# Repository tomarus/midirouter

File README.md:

FPGA/Verilog MIDI Mixer
=======================

See also: 

* https://github.com/tomarus/v-midi
* https://github.com/tomarus/midiseq

This is a "production" version of my FPGA MIDI router.

My v-midi project is more experimental, this one is tuned for my own hardware.

# Disclaimer

Do not use this to learn Verilog or FPGA stuff.

This is my own personal experimental project.

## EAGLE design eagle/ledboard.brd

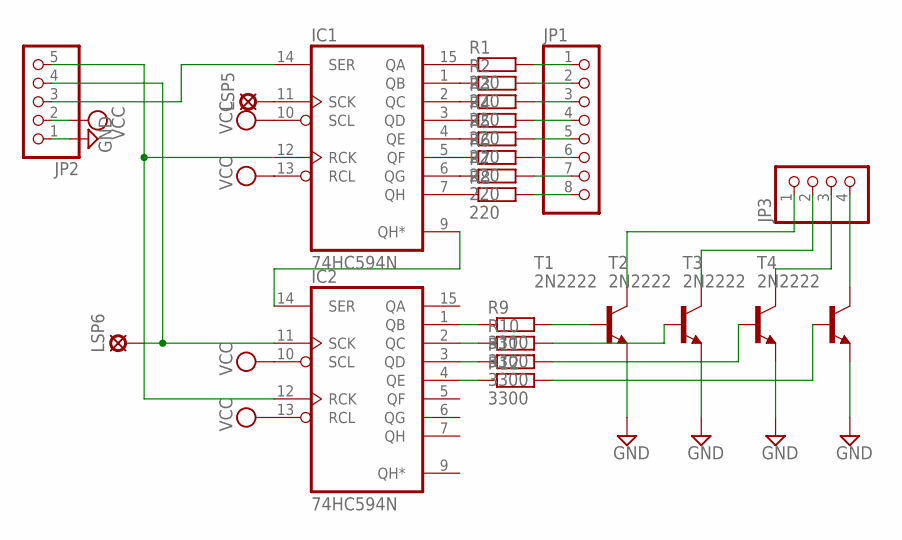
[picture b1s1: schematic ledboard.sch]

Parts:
IC1, IC2: 74HC594N; DIL16
JP1: PINHD-1X8; 1X08
JP2: PINHD-1X5; 1X05
JP3: PINHD-1X4; 1X04
LSP5, LSP6: LSP10
R1, R2, R3, R4, R5, R6, R7, R8: 220; 0207/10
R9, R10, R11, R12: 3300; 0207/10
T1, T2, T3, T4: 2N2222; TO92-EBC-OVAL

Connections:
GND: IC1.8 (GND), IC2.8 (GND), JP2.1, T1.E, T2.E, T3.E, T4.E
unnamed: IC1.14 (SER), JP2.3
unnamed: IC1.11 (SCK), LSP5.MP
unnamed: IC1.15 (QA), R1.1
unnamed: IC1.1 (QB), R2.1
unnamed: IC1.2 (QC), R3.1
unnamed: IC1.3 (QD), R4.1
unnamed: IC1.4 (QE), R5.1
unnamed: IC1.5 (QF), R6.1
unnamed: IC1.6 (QG), R7.1
unnamed: IC1.7 (QH), R8.1
unnamed: IC2.3 (QD), R11.1
unnamed: IC2.2 (QC), R10.1
unnamed: IC2.1 (QB), R9.1
unnamed: IC2.4 (QE), R12.1
unnamed: R9.2, T1.B
unnamed: R10.2, T2.B
unnamed: R11.2, T3.B
unnamed: R12.2, T4.B
unnamed: JP1.1, R1.2
unnamed: JP1.2, R2.2
unnamed: JP1.3, R3.2
unnamed: JP1.4, R4.2
unnamed: JP1.5, R5.2
unnamed: JP1.6, R6.2
unnamed: JP1.7, R7.2
unnamed: JP1.8, R8.2
unnamed: JP3.1, T1.C
unnamed: JP3.2, T2.C
unnamed: JP3.3, T3.C
unnamed: JP3.4, T4.C
unnamed: IC2.11 (SCK), JP2.4, LSP6.MP
unnamed: IC1.12 (RCK), IC2.12 (RCK), JP2.5
unnamed: IC1.9 (QH*), IC2.14 (SER)
VCC: IC1.10 (SCL), IC1.13 (RCL), IC1.16 (VCC), IC2.10 (SCL), IC2.13 (RCL), IC2.16 (VCC), JP2.2

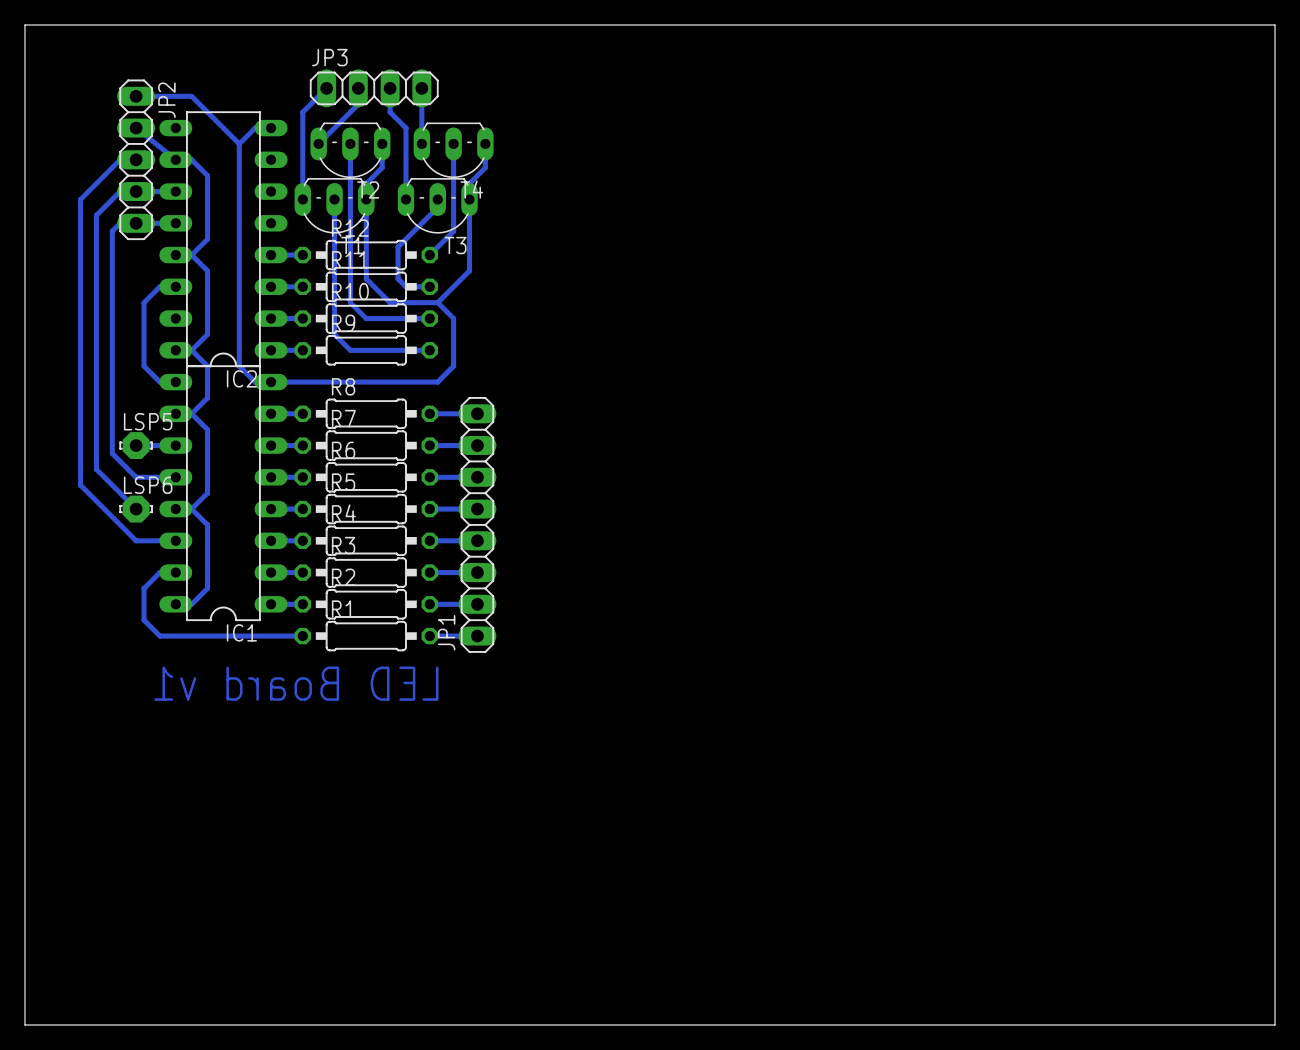
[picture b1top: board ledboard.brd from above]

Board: 2 copper layers, 100.0 x 80.0 mm, 23 parts (0 on the bottom side), 35 nets.

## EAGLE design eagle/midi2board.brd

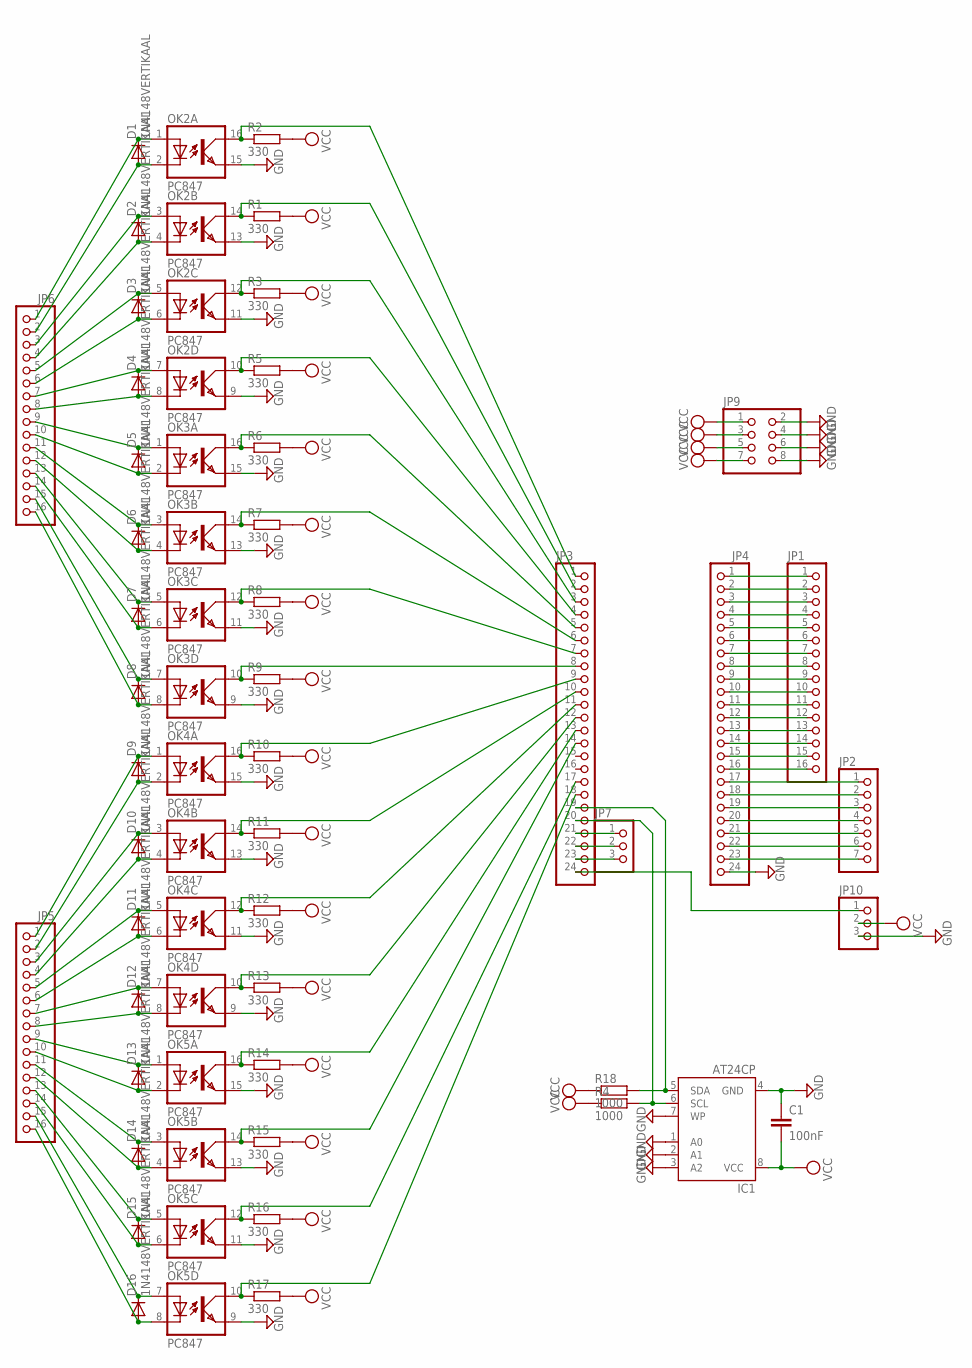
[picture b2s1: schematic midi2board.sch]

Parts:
C1: 100nF; C5B2.5
D1, D2, D3, D4, D5, D6, D7, D8, D9, D10, D11, D12, D13, D14, D15, D16: 1N4148VERTIKAAL; RAD2,5
IC1: AT24CP; DIL08
JP1, JP5, JP6: PINHD-1X16; 1X16
JP2: PINHD-1X7; 1X07
JP3, JP4: PINHD-1X24; 1X24
JP7, JP10: PINHD-1X3; 1X03
JP9: PINHD-2X4; 2X04
OK2, OK3, OK4, OK5: PC847; DIL16
R1, R2, R3, R5, R6, R7, R8, R9, R10, R11, R12, R13, R14, R15, R16, R17: 330; 0207/10
R4, R18: 1000; 0207/10

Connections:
GND: C1.1, IC1.1 (A0), IC1.2 (A1), IC1.3 (A2), IC1.4 (GND), IC1.7 (WP), JP4.24, JP9.2, JP9.4, JP9.6, JP9.8, JP10.3, OK2.9 (EMIT), OK2.11 (EMIT), OK2.13 (EMIT), OK2.15 (EMIT), OK3.9 (EMIT), OK3.11 (EMIT), OK3.13 (EMIT), OK3.15 (EMIT), OK4.9 (EMIT), OK4.11 (EMIT), OK4.13 (EMIT), OK4.15 (EMIT), OK5.9 (EMIT), OK5.11 (EMIT), OK5.13 (EMIT), OK5.15 (EMIT)
unnamed: JP2.1, JP4.17
unnamed: D1.C, JP6.1, OK2.1 (A)
unnamed: D1.A, JP6.2, OK2.2 (C)
unnamed: JP2.2, JP4.18
unnamed: JP2.3, JP4.19
unnamed: D2.C, JP6.3, OK2.3 (A)
unnamed: D2.A, JP6.4, OK2.4 (C)
unnamed: JP2.4, JP4.20
unnamed: D3.C, JP6.5, OK2.5 (A)
unnamed: D3.A, JP6.6, OK2.6 (C)
unnamed: D4.C, JP6.7, OK2.7 (A)
unnamed: D4.A, JP6.8, OK2.8 (C)
unnamed: D5.C, JP6.9, OK3.1 (A)
unnamed: D5.A, JP6.10, OK3.2 (C)
unnamed: D6.C, JP6.11, OK3.3 (A)
unnamed: D6.A, JP6.12, OK3.4 (C)
unnamed: D7.C, JP6.13, OK3.5 (A)
unnamed: D7.A, JP6.14, OK3.6 (C)
unnamed: D8.C, JP6.15, OK3.7 (A)
unnamed: D8.A, JP6.16, OK3.8 (C)
unnamed: D9.C, JP5.1, OK4.1 (A)
unnamed: D9.A, JP5.2, OK4.2 (C)
unnamed: D10.C, JP5.3, OK4.3 (A)
unnamed: D10.A, JP5.4, OK4.4 (C)
unnamed: D11.C, JP5.5, OK4.5 (A)
unnamed: D11.A, JP5.6, OK4.6 (C)
unnamed: D12.C, JP5.7, OK4.7 (A)
unnamed: D12.A, JP5.8, OK4.8 (C)
unnamed: D13.C, JP5.9, OK5.1 (A)
unnamed: D13.A, JP5.10, OK5.2 (C)
unnamed: D14.C, JP5.11, OK5.3 (A)
unnamed: D14.A, JP5.12, OK5.4 (C)
unnamed: D15.C, JP5.13, OK5.5 (A)
unnamed: D15.A, JP5.14, OK5.6 (C)
unnamed: D16.C, JP5.15, OK5.7 (A)
unnamed: D16.A, JP5.16, OK5.8 (C)
unnamed: JP3.2, OK2.14 (COL), R1.1
unnamed: JP3.1, OK2.16 (COL), R2.1
unnamed: JP3.3, OK2.12 (COL), R3.1
unnamed: JP3.4, OK2.10 (COL), R5.1
unnamed: JP3.5, OK3.16 (COL), R6.1
unnamed: JP3.6, OK3.14 (COL), R7.1
unnamed: JP3.7, OK3.12 (COL), R8.1
unnamed: JP3.8, OK3.10 (COL), R9.1
unnamed: JP3.9, OK4.16 (COL), R10.1
unnamed: JP3.10, OK4.14 (COL), R11.1
unnamed: JP3.11, OK4.12 (COL), R12.1
unnamed: JP3.12, OK4.10 (COL), R13.1
unnamed: JP3.13, OK5.16 (COL), R14.1
unnamed: JP3.14, OK5.14 (COL), R15.1
unnamed: JP3.17, OK5.12 (COL), R16.1
unnamed: JP3.18, OK5.10 (COL), R17.1
unnamed: JP3.24, JP10.1
unnamed: JP3.21, JP7.1
unnamed: JP3.22, JP7.2
unnamed: JP3.23, JP7.3
unnamed: JP1.1, JP4.1
unnamed: JP1.2, JP4.2
unnamed: JP1.3, JP4.3
unnamed: JP1.4, JP4.4
unnamed: JP1.5, JP4.5
unnamed: JP1.6, JP4.6
unnamed: JP1.7, JP4.7
unnamed: JP1.8, JP4.8
unnamed: JP1.9, JP4.9
unnamed: JP1.10, JP4.10
unnamed: JP1.11, JP4.11
unnamed: JP1.12, JP4.12
unnamed: JP1.13, JP4.13
unnamed: JP1.14, JP4.14
unnamed: JP1.15, JP4.15
unnamed: JP1.16, JP4.16
unnamed: JP2.5, JP4.21
unnamed: JP2.6, JP4.22
unnamed: JP2.7, JP4.23
unnamed: IC1.5 (SDA), JP3.19, R18.2
unnamed: IC1.6 (SCL), JP3.20, R4.2
VCC: C1.2, IC1.8 (VCC), JP9.1, JP9.3, JP9.5, JP9.7, JP10.2, R1.2, R2.2, R3.2, R4.1, R5.2, R6.2, R7.2, R8.2, R9.2, R10.2, R11.2, R12.2, R13.2, R14.2, R15.2, R16.2, R17.2, R18.1

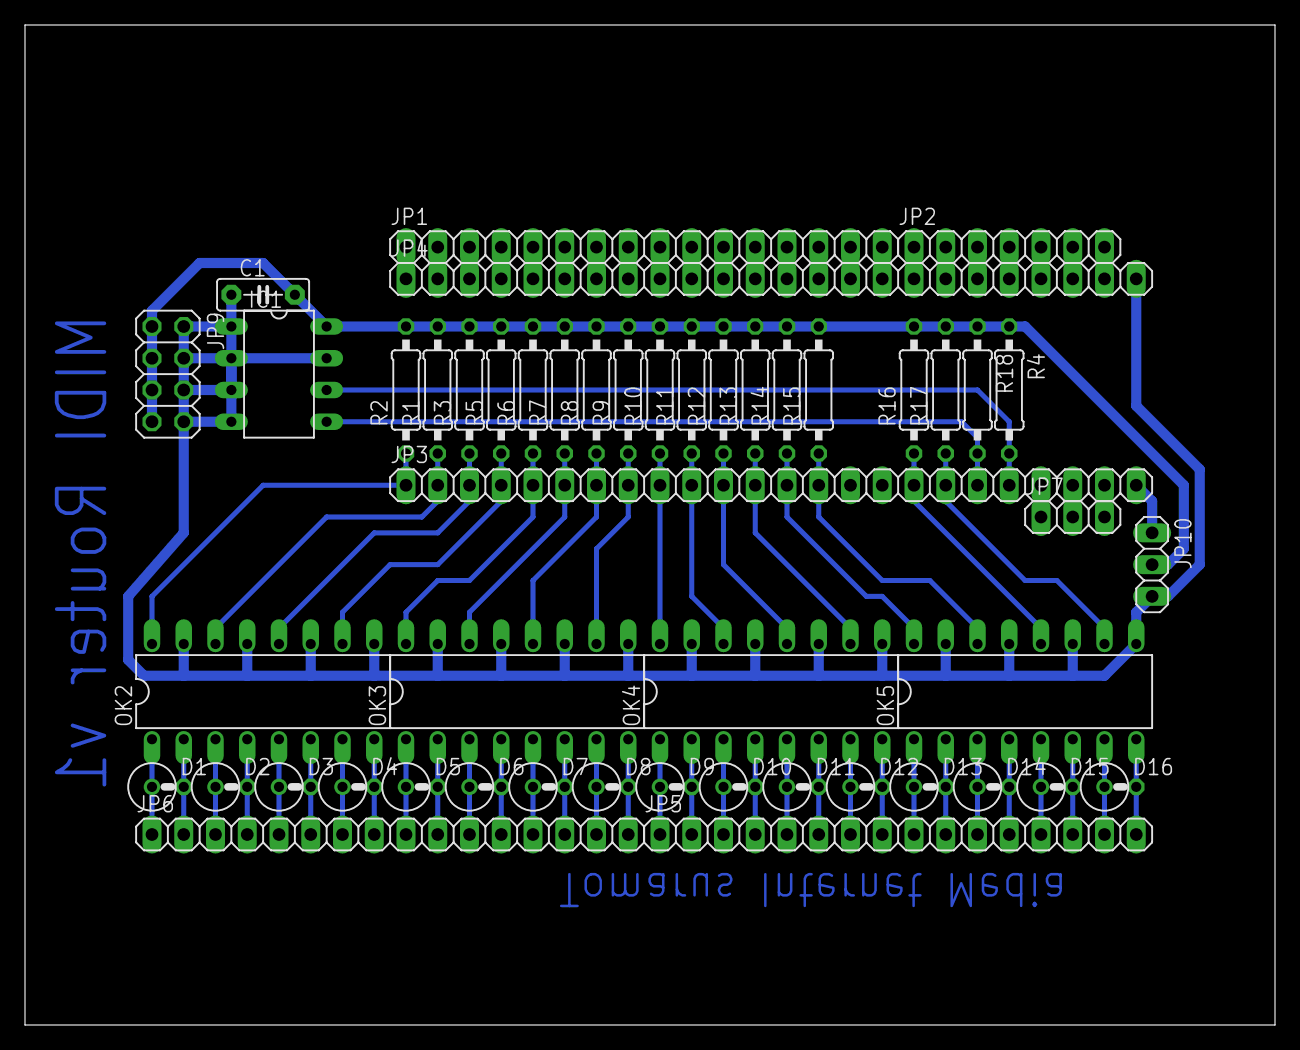
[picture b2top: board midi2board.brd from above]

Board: 2 copper layers, 100.0 x 80.0 mm, 49 parts (0 on the bottom side), 79 nets.

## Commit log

2018-07-24 Initial commit.
2018-07-25 Fix some small stuff.
2018-07-25 Reverse rows and collums for better power distribution.
2018-07-25 Remove commented out line.
2018-07-25 Improve some comments and defaults.
2018-07-31 Change activity leds duration and config to 16 ports.
2018-07-31 Add License
2018-09-02 Small updates to activity leds, avoid looping/routing on current port.
2018-09-02 Cleanup a bit.
2018-09-08 Small cleanups.
2018-10-02 Final fix leds
2018-10-02 Move around some stuff.
2018-10-02 Update project settings.
2018-10-02 Update project paths.
2018-10-03 Add screensaver.
2018-10-03 Change CLOCK to CLKS_PER_BIT.
2018-10-03 Update project files.
2018-10-03 Add (eagle) schematics and boards.
2018-10-03 Add Verilator code and some misc updates.
2018-10-03 Reformat and linter fixes.
2018-10-03 Keep our trace save file.
2018-10-07 Implement merging, more buffering, lots of other small stuff.
2018-10-07 Shave off some LUT usage using a global activity-led delay.
2018-10-08 Fix some bugs, better naming.
2018-10-08 Move around / cleanup some stuff.
2018-10-12 Make the merger work and merge everything by default.
2018-10-12 Add Go utilities midimonitor and configurator.
2018-10-14 Fix clock byte merging.
2018-10-14 Fix some warnings, fix some tabs vs spaces.
2018-10-14 More spaces vs tabs fixes.
2018-10-14 Some more identation & spaces vs tabs fixes.
2018-10-16 Fix more tabs vs spaces.
2018-10-21 Add procedural midi song generator and player.
2018-10-21 Add some startup error checking.
2018-10-21 Simplify a bit.
2018-10-21 Add piano song.
2018-10-27 Shorten led activity flicker, Fix linter warnings, Disable port 7 because its broken.
2018-10-27 Add random gates / drum sequencer.
2018-10-28 Remove test stuff, Rename onoff to gate, Fiddle with test song 3.
2018-10-28 Add soundcloud links to demo patterns.
2019-12-23 Small updates & fixes to the Go tools.
2019-12-23 Add some old pdf schematics.
2019-12-23 Try out large memory and multi-port fifos. Doesnt work atm.
2019-12-23 Add first kicad tryouts.
2019-12-23 Update gitignore.
2019-12-28 First working version using Microblaze design.
2019-12-28 Ignore clock/activesensing for activity, reduce activity length + misc fixes & updates.
2019-12-28 Remove metadata.
2019-12-29 Fix clock merging, smallish other updates.
2019-12-30 Fix clock detection.
2020-01-01 Work on schematics and pcbs.
2020-01-02 Increase mem from 32k to 64k, Add xspi flash config management.
2020-01-02 Add sysex processing, info + dump command.
2020-01-02 Fix/Update minor stuff.
2020-01-03 Work on pcbs a bit.
2020-01-04 More work on pcbs and frontpanel.
2020-01-04 Switch to TCMT4600 and increase size of ferrites.
2020-01-07 Work on base pcb/schematics + frontpanel.
2020-01-14 Updates to frontpanels, schematics and pcbs.
2020-01-15 Move all kicad stuff to kicad/ dir.
2020-01-15 Remove old Eagle files.
2020-01-15 Fix for last commit.
2020-01-15 Fix for last commit, and the one before that.
2020-01-15 Silkscreen and text updates.
2020-01-26 Some minor silkscreen updates.
2020-04-26 Revision A PCBs.
2020-05-30 New design, update LED driver for 595.
2020-05-30 Add LED/Port identification command.
2020-06-02 Swap Input and Output for activity LEDs.
